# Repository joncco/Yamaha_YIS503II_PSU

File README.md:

# Universal Vintage Computer Power Supply
Idea for a "universal" power supply, either internal external, for different systems that require multiple input voltages (like 8080-based systems, or the BBC Model B).<br>

It's nothing groundbreaking, unique or even clever - it just uses off-the-shelf integrated components to generate the additional voltages.<br>

Expects regulated +12VDC input (rated at ≥5A).<br>

Passes through the +12VDC (≥400mA depending on input supply) and additionally outputs:
- Regulated +5VDC (max. 4A)
- Regulated -12VDC (max. 80mA)
- Regulated -5VDC (max. 500mA)

If the additional voltages are not required then they can be excluded from the build.<br>

Prevents reverse-polarity source input with a MOSFET (can be excluded if not required).<br>

The PCB measures 70x50mm and has M3 mounting holes in the corners (offset 42 & 62mm).<br>

## [Data Sheets](/Datasheets)
Relevant data sheets to save you hunting around for the parts or trying to figure out replacements.

## [KiCad & Fabrication Files](/Universal_Modern_PSU_12V_Input)
KiCad 10 design files plus fabrication (Gerber) files

## Status
21-Nov-2025: Still tweaking the design before getting test boards made - current design should work but would like to improve further if possible

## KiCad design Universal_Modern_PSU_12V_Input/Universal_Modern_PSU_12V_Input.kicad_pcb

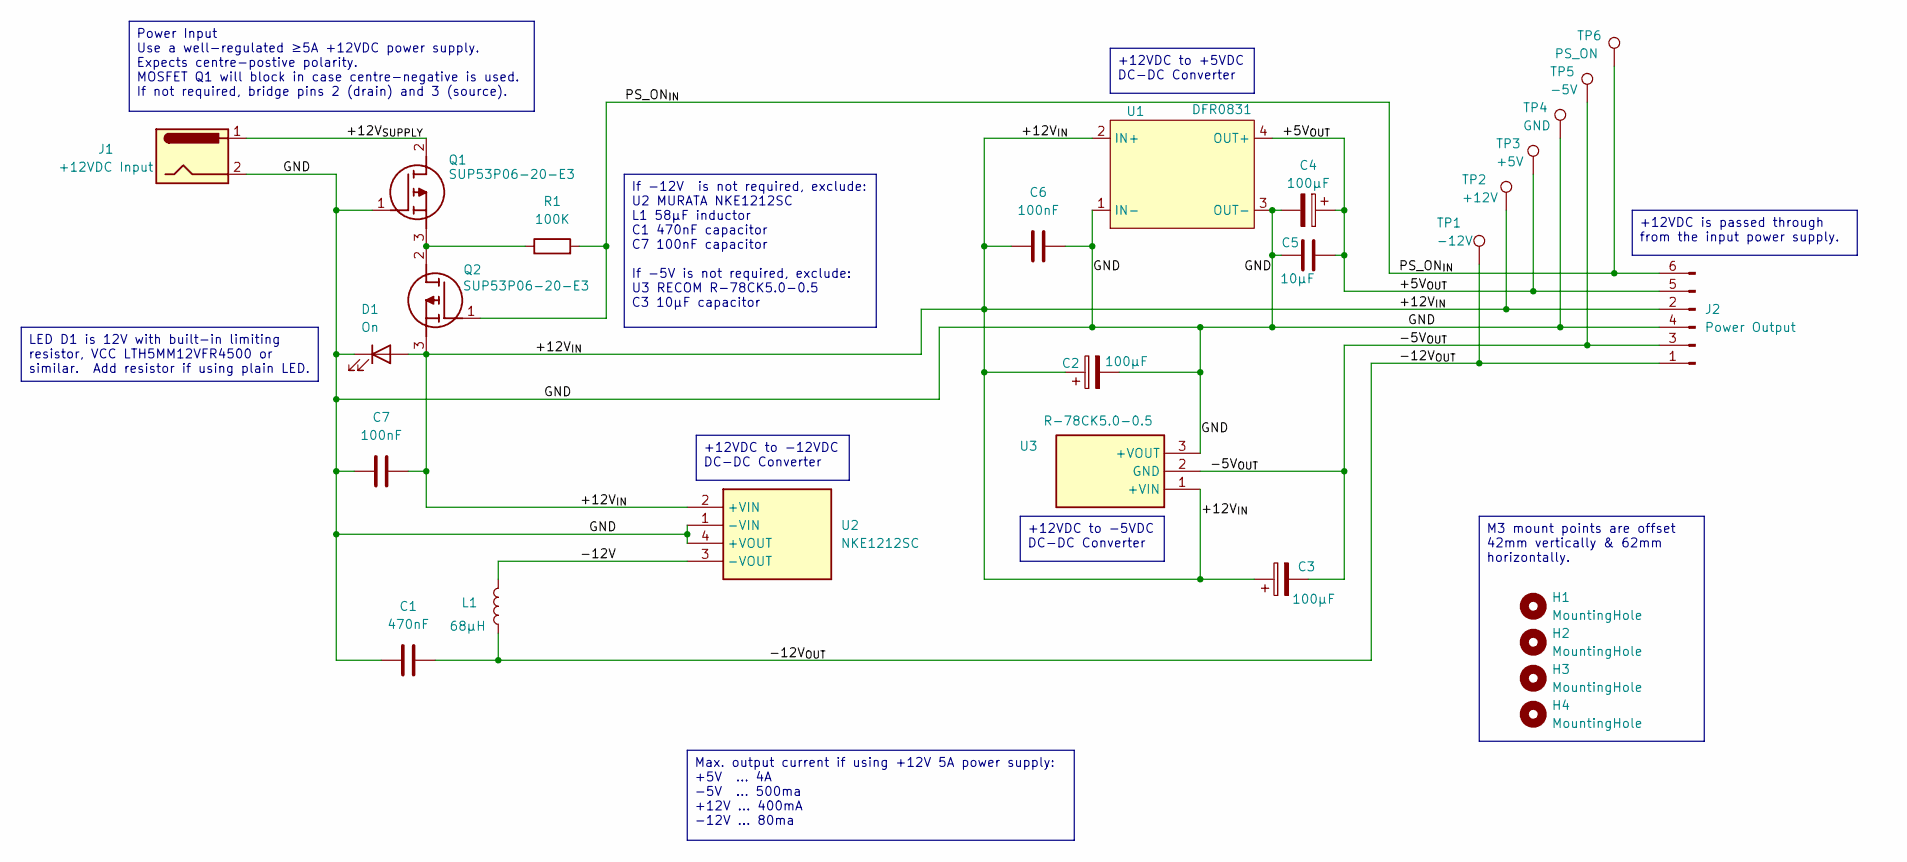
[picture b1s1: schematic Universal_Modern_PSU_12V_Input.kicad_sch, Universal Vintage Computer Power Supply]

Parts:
C1: 470nF; C_Disc_D5.0mm_W2.5mm_P5.00mm
C2, C3, C4: 100µF; CP_Radial_D8.0mm_P5.00mm
C5: 10µF; C_Disc_D5.0mm_W2.5mm_P5.00mm
C6, C7: 100nF; C_Disc_D5.0mm_W2.5mm_P5.00mm
D1: On; PinHeader_1x02_P2.54mm_Vertical
H1, H2, H3, H4: MountingHole; MountingHole_3.2mm_M3
J1: +12VDC Input; 6404452
J2: Power Output; 640445-6
L1: 68µH; 22R683C
Q1, Q2: SUP53P06-20-E3; TO254P465X1028X1931-3P; Mouser Part Number 781-SUP53P06-20-E3
R1: 100K
TP1: -12V; TestPoint_Pad_D2.5mm
TP2: +12V; TestPoint_Pad_D2.5mm
TP3: +5V; TestPoint_Pad_D2.5mm
TP4: GND; TestPoint_Pad_D2.5mm
TP5: -5V; TestPoint_Pad_D2.5mm
TP6: PS_ON; TestPoint_Pad_D2.5mm
U1: DFR0831
U2: NKE1212SC; Manufacturer_Part_Number NKE1212SC
U3: R-78CK5.0-0.5; R78CK5005; Manufacturer_Part_Number R-78CK5.0-0.5

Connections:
/+5V_{OUT}: C4.1, C5.2, J2.5, TP3.1 (1_1), U1.4 (OUT+)
/+12V_{IN}: C2.1, C3.1, C6.1, C7.2, D1.2 (A), J2.2, Q2.3 (S), TP2.1 (1_1), U1.2 (IN+), U2.2 (+VIN), U3.1 (+VIN)
/+12V_{SUPPLY}: J1.1, Q1.2 (D)
/-5V_{OUT}: C3.2, J2.3, TP5.1 (1_1), U3.2 (GND)
/-12V: L1.2, U2.3 (-VOUT)
/-12V_{OUT}: C1.2, J2.1, L1.1, TP1.1 (1_1)
/GND: C1.1, C2.2, C4.2, C5.1, C6.2, C7.1, D1.1 (K), J1.2, J2.4, Q1.1 (G), TP4.1 (1_1), U1.1 (IN-), U1.3 (OUT-), U2.1 (-VIN), U2.4 (+VOUT), U3.3 (+VOUT)
/PS_ON_{IN}: J2.6, Q2.1 (G), R1.2, TP6.1 (1_1)
unnamed: Q1.3 (S), Q2.2 (D), R1.1

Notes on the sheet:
If -12V is not required, exclude: U2 MURATA NKE1212SC L1 58µF inductor C1 470nF capacitor C7 100nF capacitor If -5V is not required, exclude: U3 RECOM R-78CK5.0-0.5 C3 10µF capacitor
+12VDC to -12VDC DC-DC Converter
Max. output current if using +12V 5A power supply: +5V ... 4A -5V ... 500ma +12V ... 400mA -12V ... 80ma
Power Input Use a well-regulated ≥5A +12VDC power supply. Expects centre-postive polarity. MOSFET Q1 will block in case centre-negative is used. If not required, bridge pins 2 (drain) and 3 (source).
LED D1 is 12V with built-in limiting resistor, VCC LTH5MM12VFR4500 or similar. Add resistor if using plain LED.
M3 mount points are offset 42mm vertically & 62mm horizontally.
+12VDC to +5VDC DC-DC Converter
+12VDC is passed through from the input power supply.
+12VDC to -5VDC DC-DC Converter

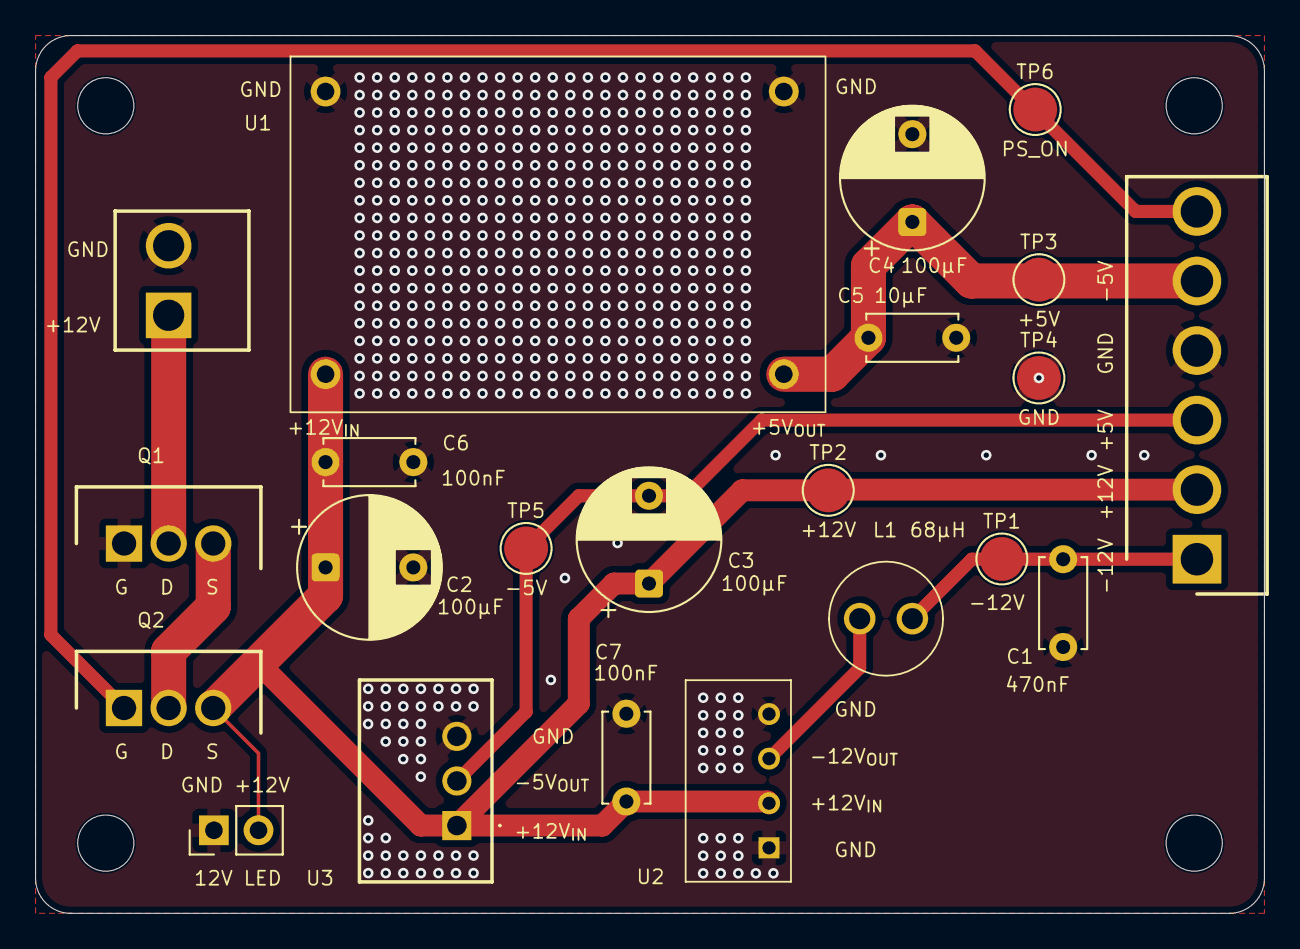
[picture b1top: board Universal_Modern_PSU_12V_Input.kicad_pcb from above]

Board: 2 copper layers, 70.0 x 50.0 mm, 26 parts (0 on the bottom side), 9 nets.

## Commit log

2025-11-21 Minor updates
2025-11-21 Moved file
2025-11-21 Move file
2025-11-21 Added additional capacitors
2025-11-21 Added mount point offsets to schematic
2025-11-21 Additional information on schematic
2025-11-21 Thickened +5V & +12V tracks
2025-11-21 Additional vias for heat conduction
2025-11-21 Minor PCB & schematic changes
2025-11-22 Further refinements to PCB layout
2026-04-17 Add PS_ON soft-on pin
2026-04-17 Update schematic pdf
2026-04-17 Add original Q1 back.
2026-04-17 Remove extra wire in Q1
2026-04-17 Add net labels for PS_ON
2026-04-20 Add footprint for connector
2026-04-20 Fix pin order of output header
2026-04-20 Implement schematic changes to PCB
2026-04-20 Fix header pin order
2026-04-20 Update 3d render
2026-04-20 Update KiCad version in README
    Updated KiCad version from 9 to 10 in the README.
2026-04-21 Update KiCad & Fabrication Files link in README
2026-04-21 Generate interactive BOM
